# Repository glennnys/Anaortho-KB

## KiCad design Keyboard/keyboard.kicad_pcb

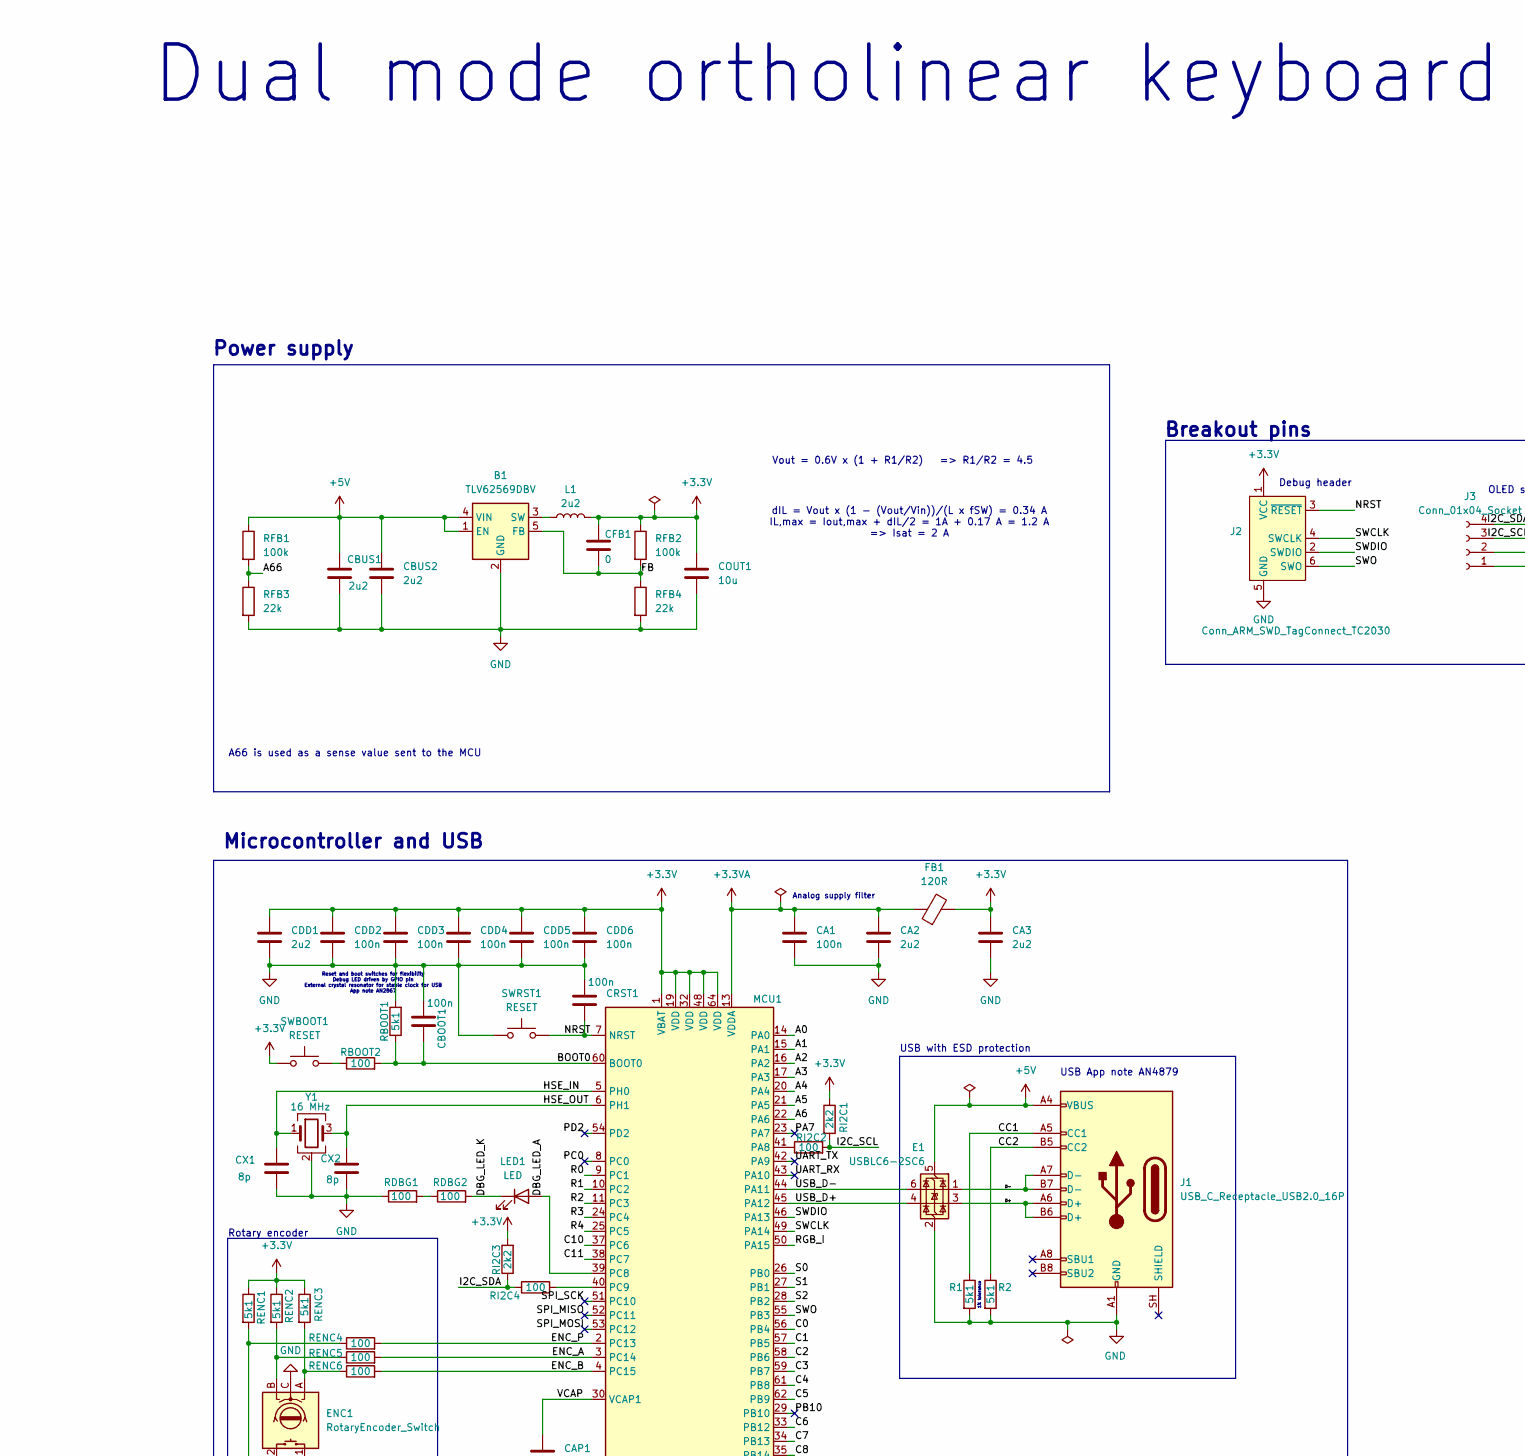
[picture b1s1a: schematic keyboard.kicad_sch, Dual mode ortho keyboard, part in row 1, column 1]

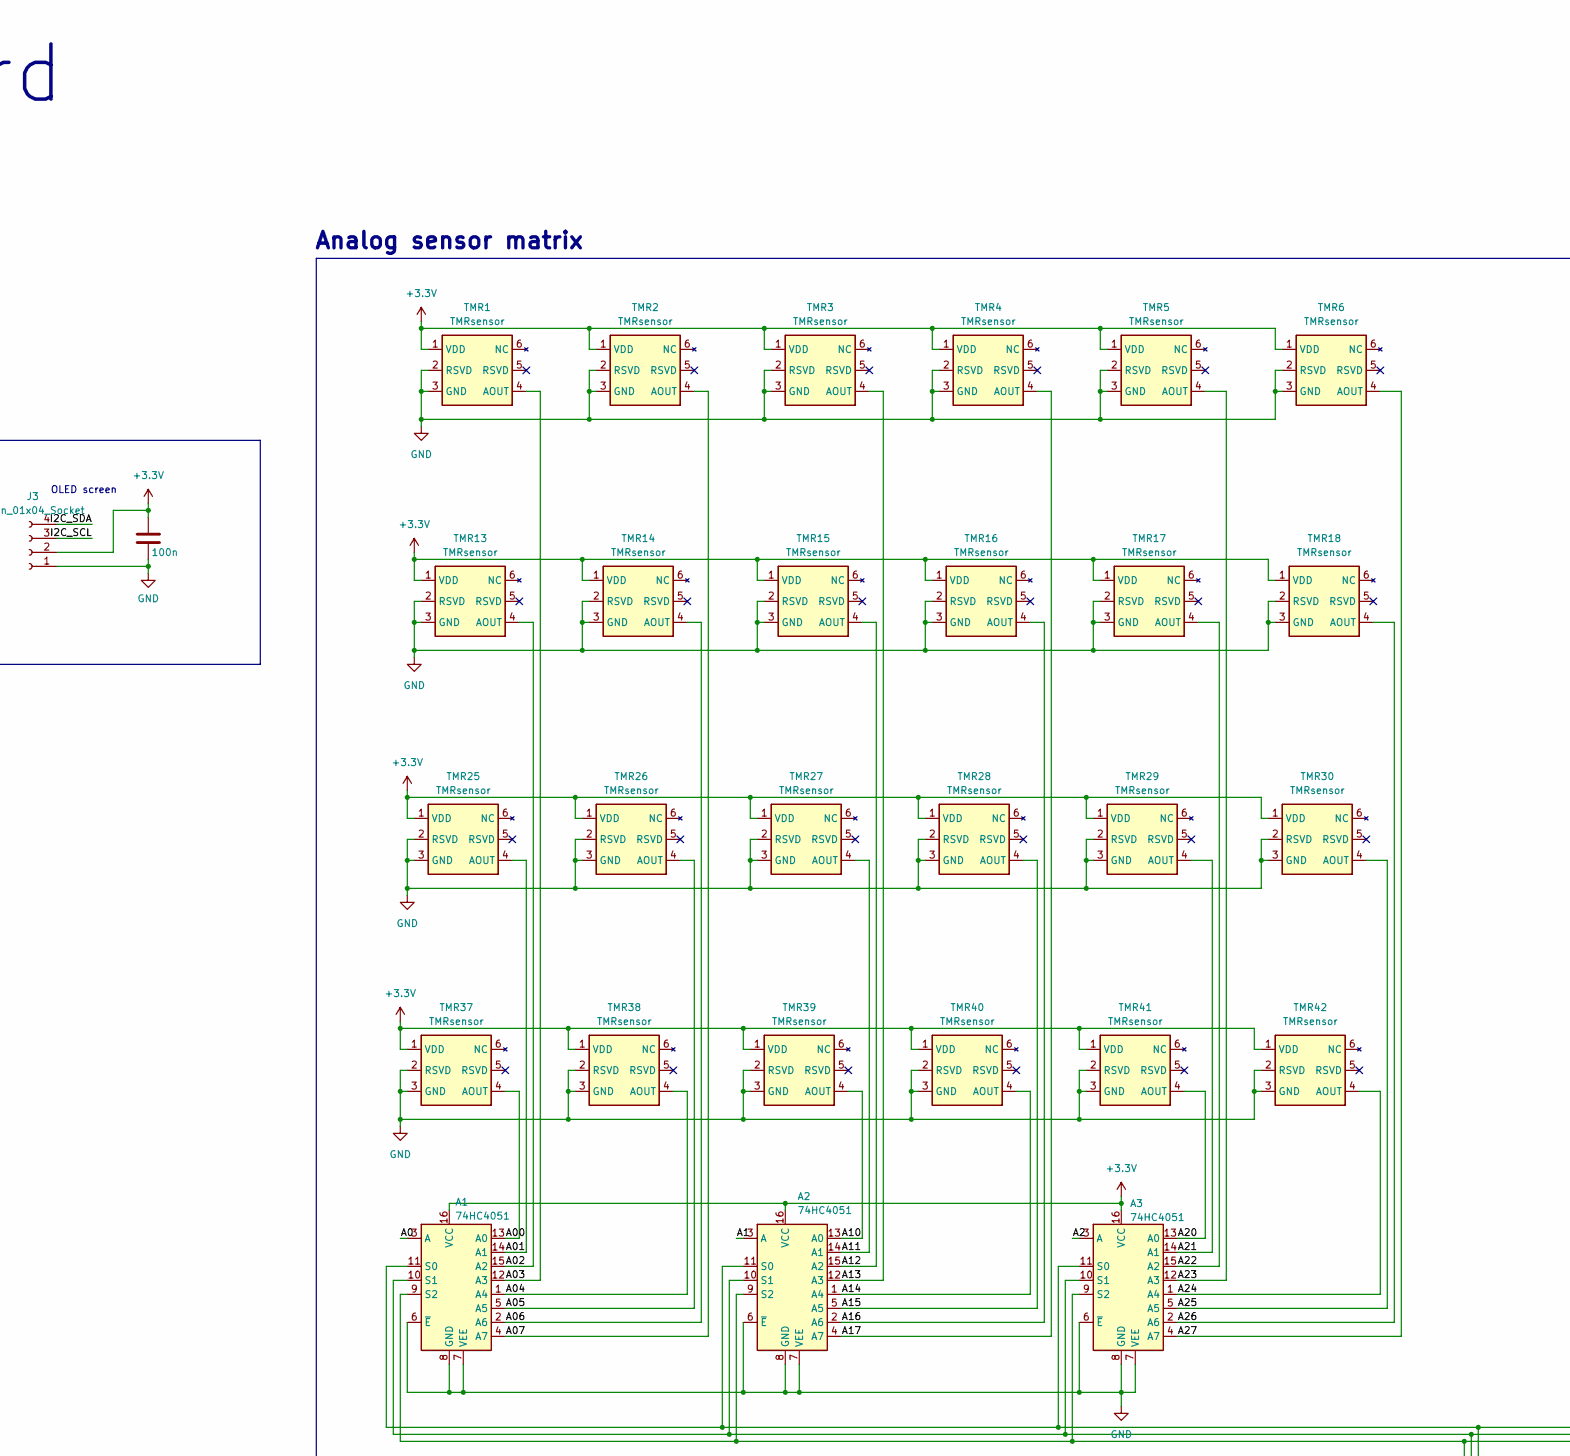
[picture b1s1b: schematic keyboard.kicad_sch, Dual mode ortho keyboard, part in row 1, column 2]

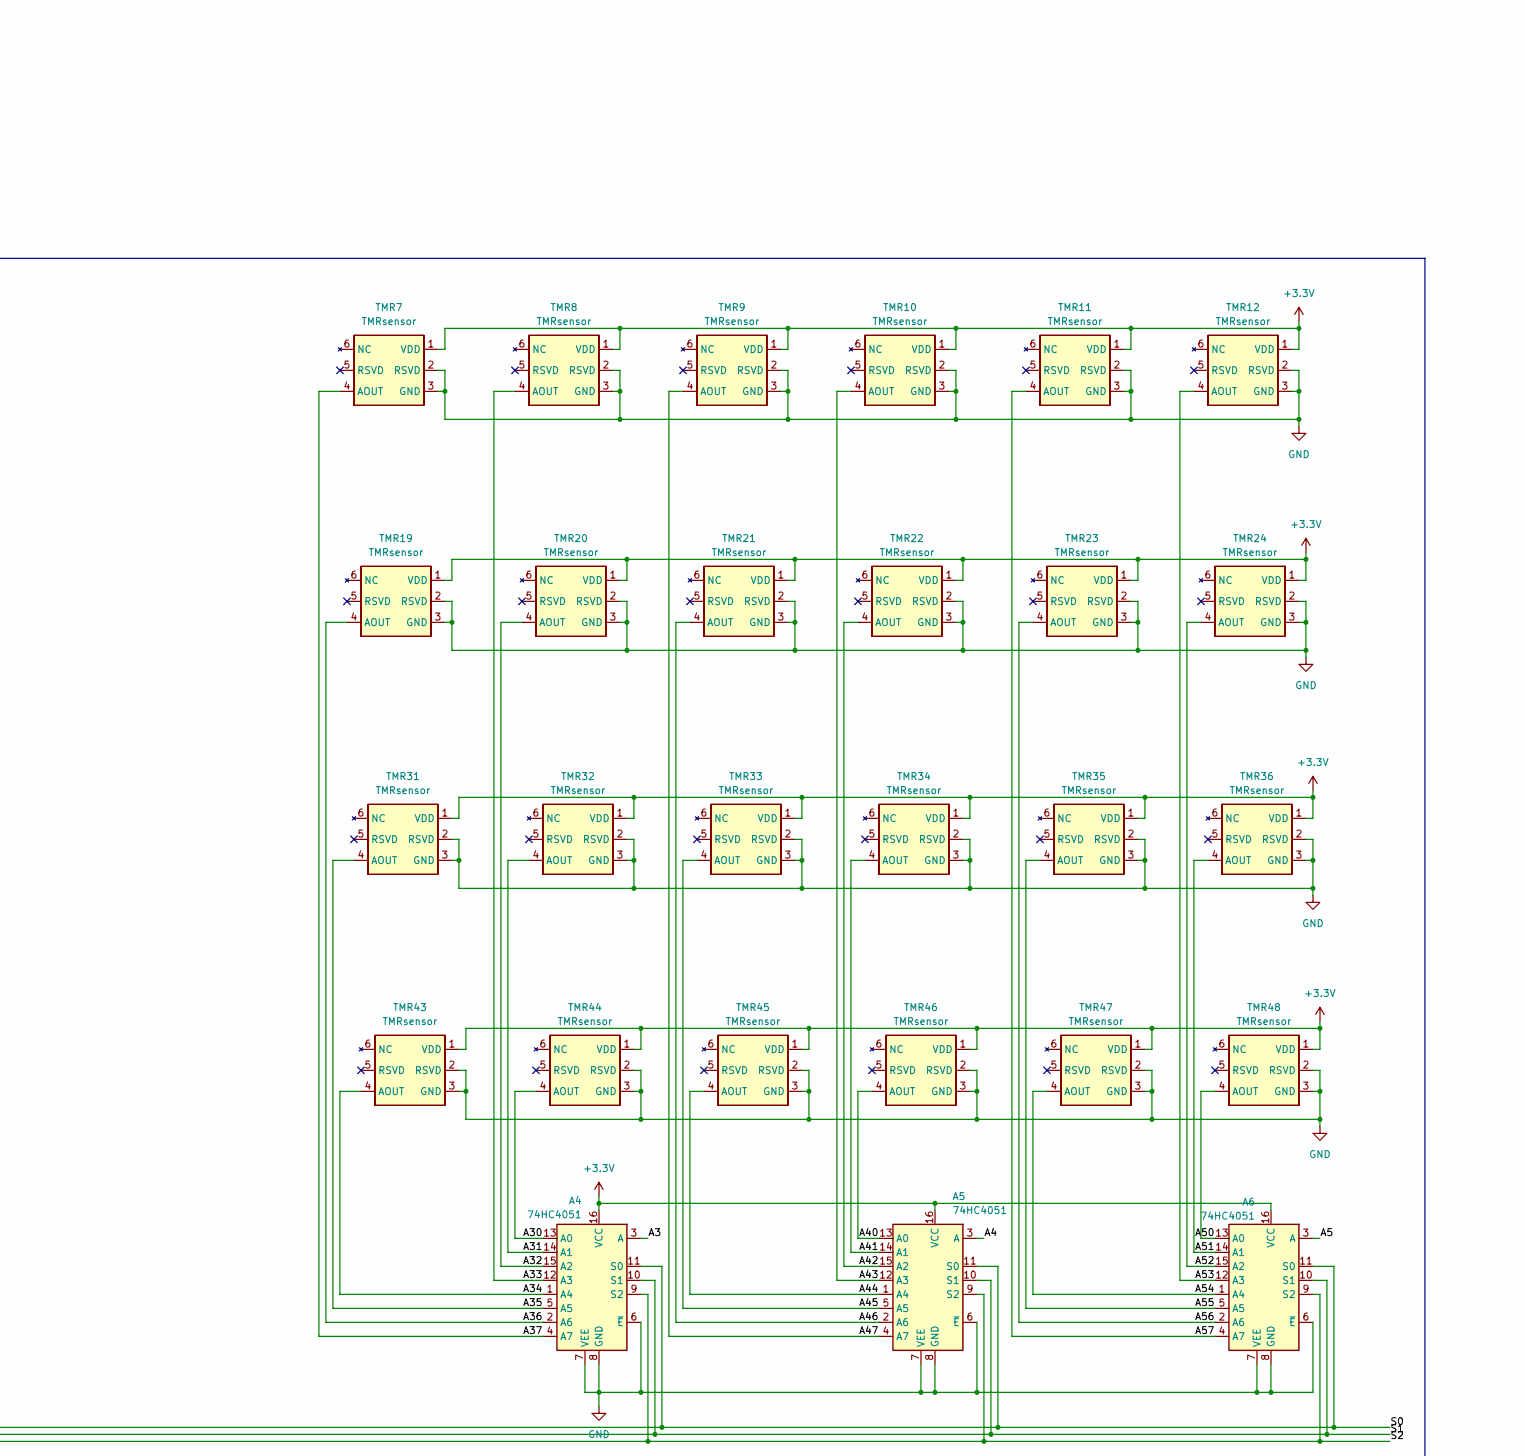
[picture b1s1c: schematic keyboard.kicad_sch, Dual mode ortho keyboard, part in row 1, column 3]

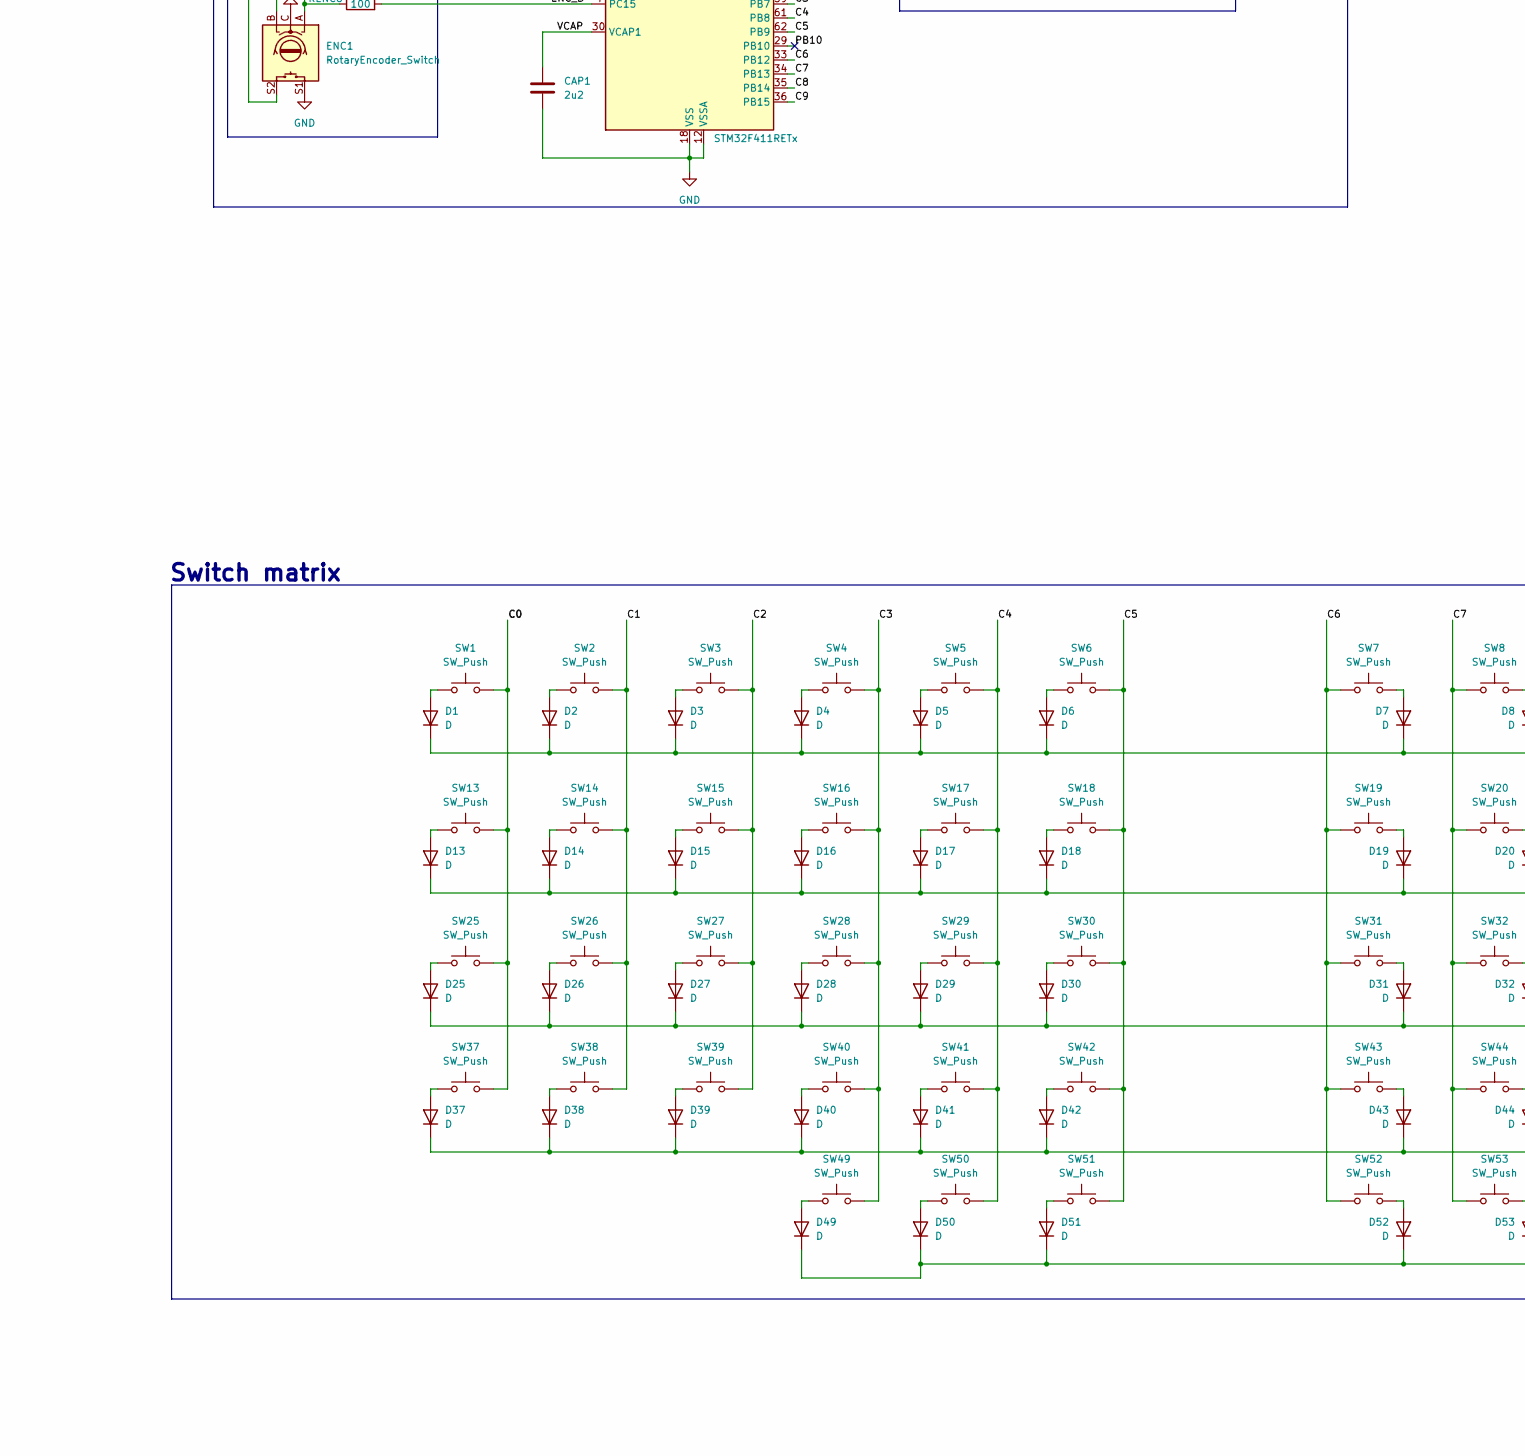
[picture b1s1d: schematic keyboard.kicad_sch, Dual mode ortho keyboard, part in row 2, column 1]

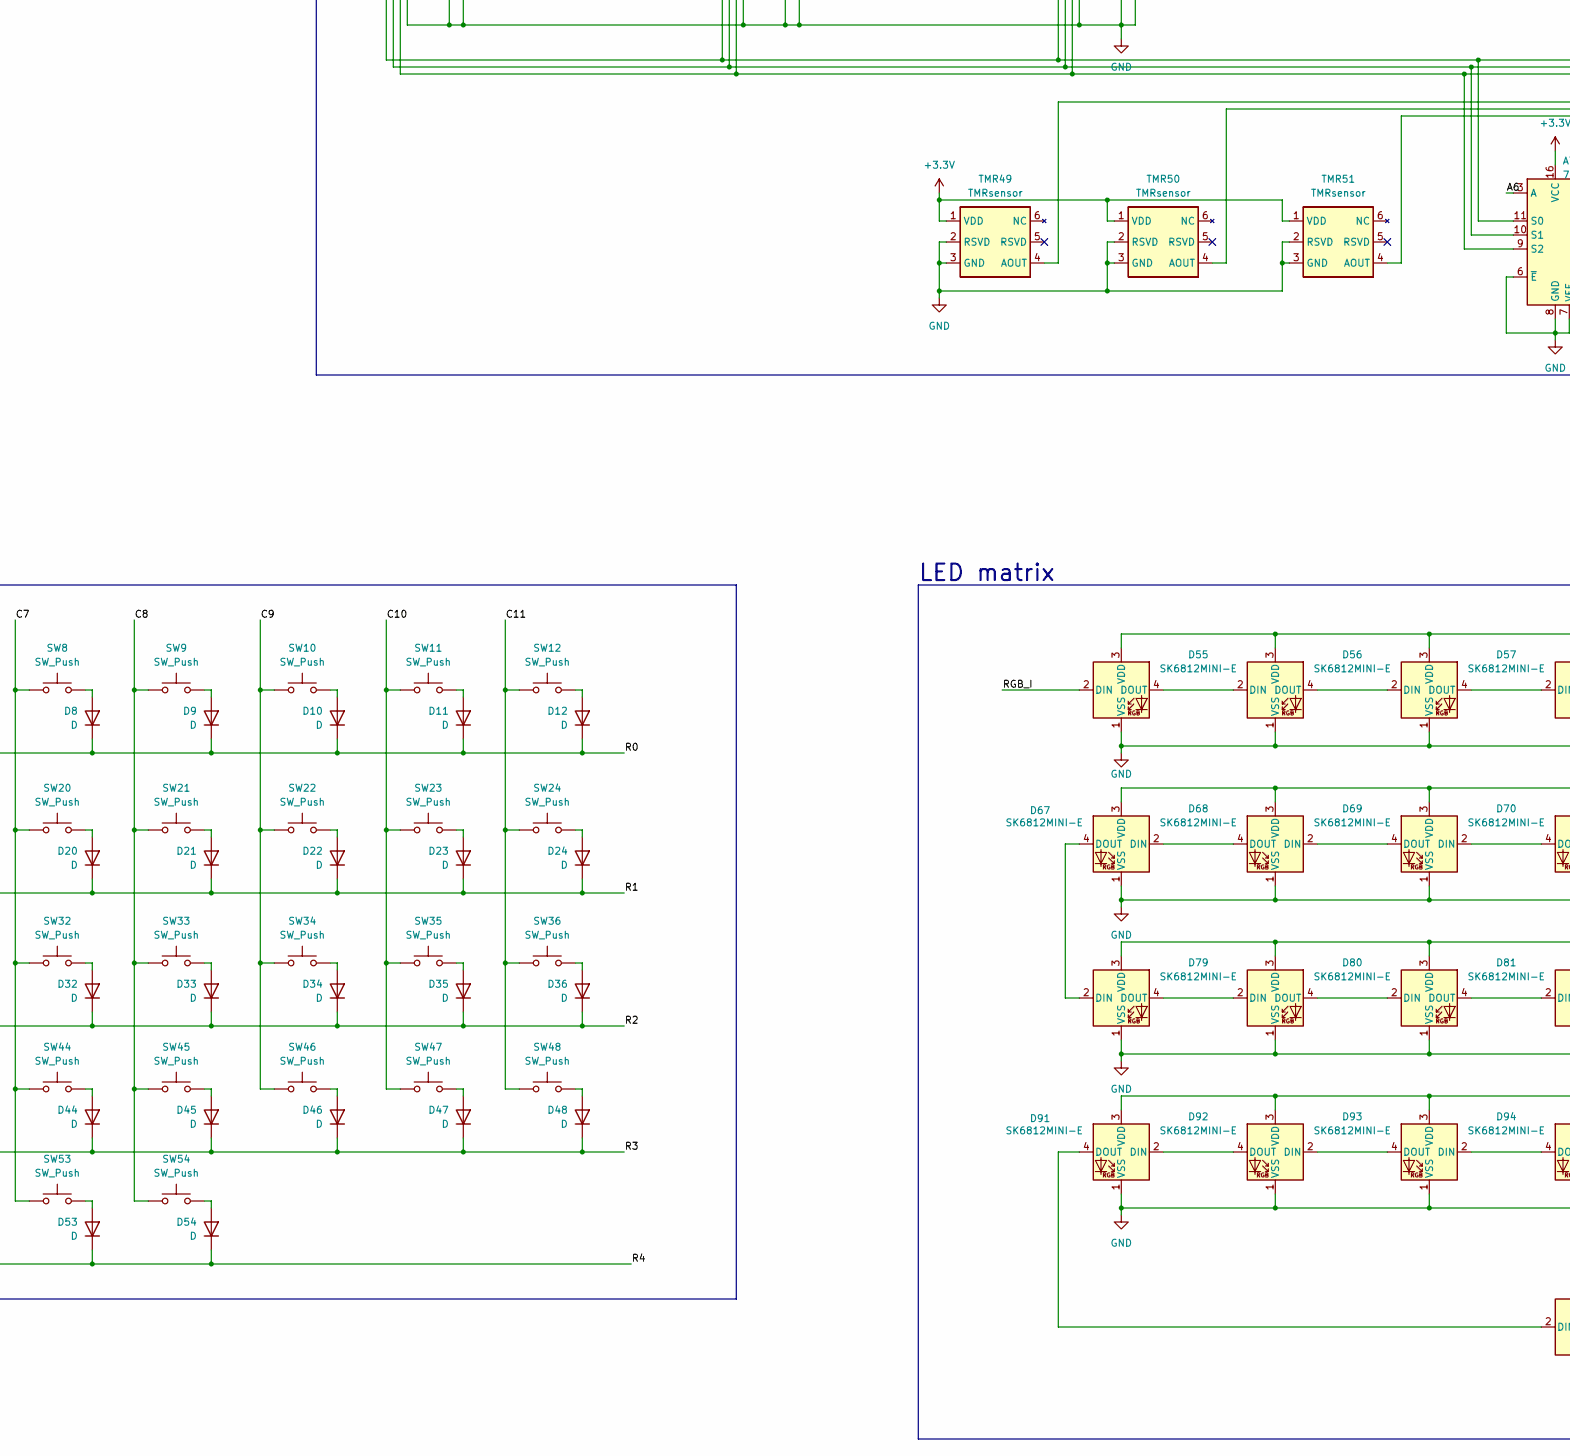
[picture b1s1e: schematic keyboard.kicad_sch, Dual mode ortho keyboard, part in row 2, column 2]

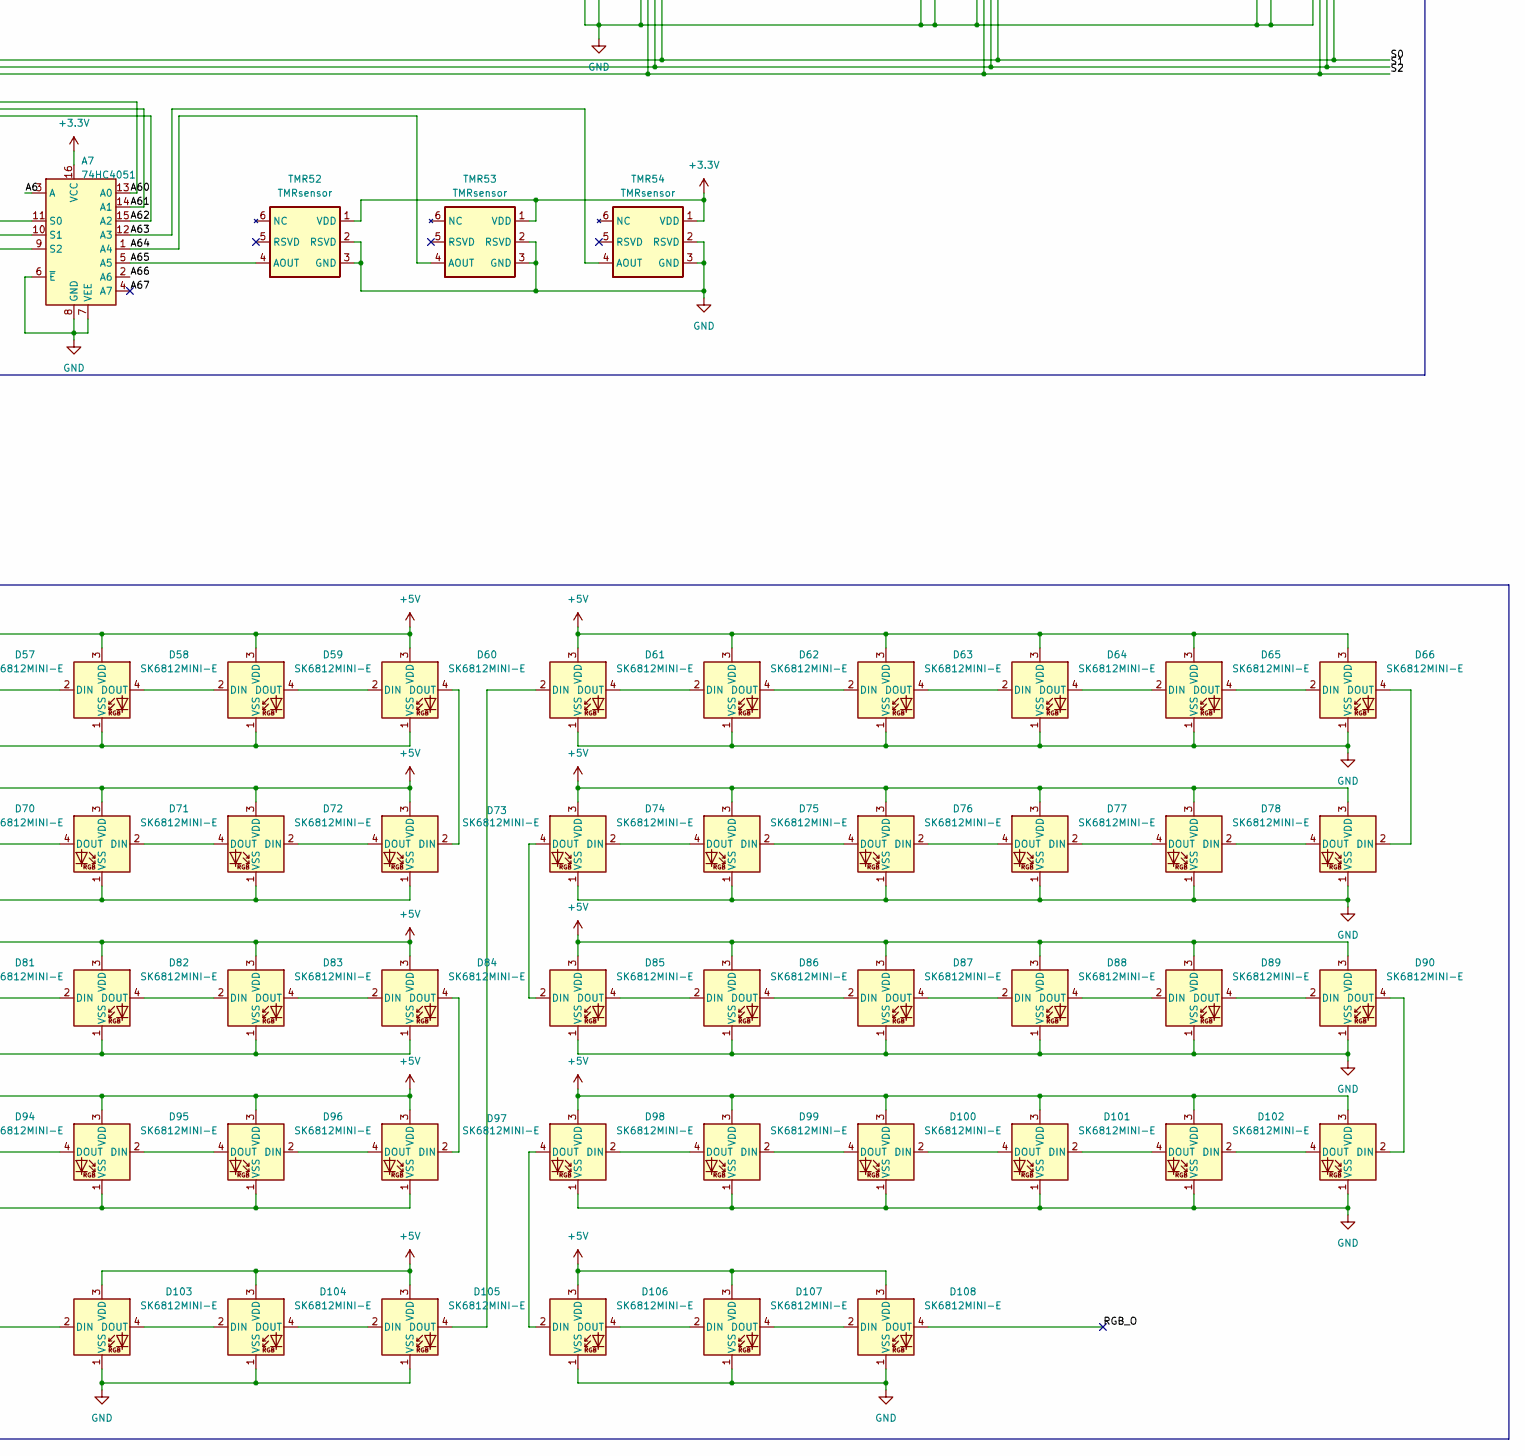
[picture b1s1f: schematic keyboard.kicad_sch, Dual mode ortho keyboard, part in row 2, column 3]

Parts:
A1, A2, A3, A4, A5, A6, A7: 74HC4051; SOIC-16W_5.3x10.2mm_P1.27mm
B1: TLV62569DBV; SOT-23-5
CA1: 100n; C_0402_1005Metric
CA2, CA3: 2u2; C_0603_1608Metric
CAP1: 2u2; C_0603_1608Metric
CBOOT1: 100n; C_0402_1005Metric
CBUS1, CBUS2: 2u2; C_0603_1608Metric
CDD1: 2u2; C_0603_1608Metric
CDD2, CDD3, CDD4, CDD5, CDD6: 100n; C_0402_1005Metric
CFB1: 0; C_0402_1005Metric
COLED1: 100n; C_0402_1005Metric
COUT1: 10u; C_0805_2012Metric
CRST1: 100n; C_0402_1005Metric
CX1, CX2: 8p; C_0402_1005Metric
D1, D2, D3, D4, D5, D6, D7, D8, D9, D10, D11, D12, D13, D14, D15, D16, D17, D18, D19, D20, D21, D22, D23, D24, D25, D26, D27, D28, D29, D30, D31, D32, D33, D34, D35, D36, D37, D38, D39, D40, D41, D42, D43, D44, D45, D46, D47, D48, D49, D50, D51, D52, D53, D54: D; D_SOD-123
D55, D56, D57, D58, D59, D60, D61, D62, D63, D64, D65, D66, D67, D68, D69, D70, D71, D72, D73, D74, D75, D76, D77, D78, D79, D80, D81, D82, D83, D84, D85, D86, D87, D88, D89, D90, D91, D92, D93, D94, D95, D96, D97, D98, D99, D100, D101, D102, D103, D104, D105, D106, D107, D108: SK6812MINI-E; LED_SK6812MINI-E_3.2x2.8mm_P1.5mm_ReverseMount
E1: USBLC6-2SC6; SOT-23-6
ENC1: RotaryEncoder_Switch; RotaryEncoder_Alps_EC11E-Switch_Vertical_H20mm
FB1: 120R; L_0603_1608Metric
J1: USB_C_Receptacle_USB2.0_16P; USB_C_Receptacle_GCT_USB4105-xx-A_16P_TopMnt_Horizontal
J2: Conn_ARM_SWD_TagConnect_TC2030; Tag-Connect_TC2030-IDC-FP_2x03_P1.27mm_Vertical
J3: Conn_01x04_Socket; PinSocket_1x04_P2.54mm_Vertical
L1: 2u2; L_0805_2012Metric
LED1: LED; LED_D4.0mm
MCU1: STM32F411RETx; LQFP-64_10x10mm_P0.5mm
R1, R2: 5k1; R_0402_1005Metric
RBOOT1: 5k1; R_0402_1005Metric
RBOOT2: 100; R_0402_1005Metric
RDBG1, RDBG2: 100; R_0402_1005Metric
RENC1, RENC2, RENC3: 5k1; R_0402_1005Metric
RENC4, RENC5, RENC6: 100; R_0402_1005Metric
RFB1, RFB2: 100k; R_0402_1005Metric
RFB3, RFB4: 22k; R_0402_1005Metric
RI2C1, RI2C3: 2k2; R_0402_1005Metric
RI2C2, RI2C4: 100; R_0402_1005Metric
SW1, SW2, SW3, SW4, SW5, SW6, SW7, SW8, SW9, SW10, SW11, SW12, SW13, SW14, SW15, SW16, SW17, SW18, SW19, SW20, SW21, SW22, SW23, SW24, SW25, SW26, SW27, SW28, SW29, SW30, SW31, SW32, SW33, SW34, SW35, SW36, SW37, SW38, SW39, SW40, SW41, SW42, SW43, SW44, SW45, SW46, SW47, SW48, SW49, SW50, SW51, SW52, SW53, SW54: SW_Push; SW_Cherry_MX_1.00u_PCB
SWBOOT1: RESET; SW_PUSH_6mm
SWRST1: RESET; SW_PUSH_6mm
TMR1, TMR2, TMR3, TMR4, TMR5, TMR6, TMR7, TMR8, TMR9, TMR10, TMR11, TMR12, TMR13, TMR14, TMR15, TMR16, TMR17, TMR18, TMR19, TMR20, TMR21, TMR22, TMR23, TMR24, TMR25, TMR26, TMR27, TMR28, TMR29, TMR30, TMR31, TMR32, TMR33, TMR34, TMR35, TMR36, TMR37, TMR38, TMR39, TMR40, TMR41, TMR42, TMR43, TMR44, TMR45, TMR46, TMR47, TMR48, TMR49, TMR50, TMR51, TMR52, TMR53, TMR54: TMRsensor; SOT-23-6
Y1: 16 MHz; Crystal_SMD_3225-4Pin_3.2x2.5mm

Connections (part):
+3.3V: A1.16 (VCC), A2.16 (VCC), A3.16 (VCC), A4.16 (VCC), A5.16 (VCC), A6.16 (VCC), A7.16 (VCC), CA3.1, CDD1.1, CDD2.1, CDD3.1, CDD4.1, CDD5.1, CDD6.1, CFB1.1, COLED1.1, COUT1.1, FB1.2, J2.1 (VCC), J3.2, L1.2, MCU1.1 (VBAT), MCU1.19 (VDD), MCU1.32 (VDD), MCU1.48 (VDD), MCU1.64 (VDD), RENC1.1, RENC2.1, RENC3.1, RFB2.1, RI2C1.1, RI2C3.2, SWBOOT1.1, TMR1.1 (VDD), TMR2.1 (VDD), TMR3.1 (VDD), TMR4.1 (VDD), TMR5.1 (VDD), TMR6.1 (VDD), TMR7.1 (VDD), TMR8.1 (VDD), TMR9.1 (VDD), TMR10.1 (VDD), TMR11.1 (VDD), TMR12.1 (VDD), TMR13.1 (VDD), TMR14.1 (VDD), TMR15.1 (VDD), TMR16.1 (VDD), TMR17.1 (VDD), TMR18.1 (VDD), TMR19.1 (VDD), TMR20.1 (VDD), TMR21.1 (VDD), TMR22.1 (VDD), TMR23.1 (VDD), TMR24.1 (VDD), TMR25.1 (VDD), TMR26.1 (VDD), TMR27.1 (VDD), TMR28.1 (VDD), TMR29.1 (VDD), TMR30.1 (VDD), TMR31.1 (VDD), TMR32.1 (VDD), TMR33.1 (VDD), TMR34.1 (VDD), TMR35.1 (VDD), TMR36.1 (VDD), TMR37.1 (VDD), TMR38.1 (VDD), TMR39.1 (VDD), TMR40.1 (VDD), TMR41.1 (VDD), TMR42.1 (VDD), TMR43.1 (VDD), TMR44.1 (VDD), TMR45.1 (VDD), TMR46.1 (VDD), TMR47.1 (VDD)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
+3.3VA: CA1.1, CA2.1, FB1.1, MCU1.13 (VDDA)
+5V: B1.1 (EN), B1.4 (VIN), CBUS1.1, CBUS2.1, D55.3 (VDD), D56.3 (VDD), D57.3 (VDD), D58.3 (VDD), D59.3 (VDD), D60.3 (VDD), D61.3 (VDD), D62.3 (VDD), D63.3 (VDD), D64.3 (VDD), D65.3 (VDD), D66.3 (VDD), D67.3 (VDD), D68.3 (VDD), D69.3 (VDD), D70.3 (VDD), D71.3 (VDD), D72.3 (VDD), D73.3 (VDD), D74.3 (VDD), D75.3 (VDD), D76.3 (VDD), D77.3 (VDD), D78.3 (VDD), D79.3 (VDD), D80.3 (VDD), D81.3 (VDD), D82.3 (VDD), D83.3 (VDD), D84.3 (VDD), D85.3 (VDD), D86.3 (VDD), D87.3 (VDD), D88.3 (VDD), D89.3 (VDD), D90.3 (VDD), D91.3 (VDD), D92.3 (VDD), D93.3 (VDD), D94.3 (VDD), D95.3 (VDD), D96.3 (VDD), D97.3 (VDD), D98.3 (VDD), D99.3 (VDD), D100.3 (VDD), D101.3 (VDD), D102.3 (VDD), D103.3 (VDD), D104.3 (VDD), D105.3 (VDD), D106.3 (VDD), D107.3 (VDD), D108.3 (VDD), E1.5 (VBUS), J1.A4 (VBUS), J1.A9 (VBUS), J1.B4 (VBUS), J1.B9 (VBUS), RFB1.1
/A0: A1.3 (A), MCU1.14 (PA0)
/A00: A1.13 (A0), TMR37.4 (AOUT)
/A1: A2.3 (A), MCU1.15 (PA1)
/A01: A1.14 (A1), TMR25.4 (AOUT)
/A2: A3.3 (A), MCU1.16 (PA2)
/A02: A1.15 (A2), TMR13.4 (AOUT)
/A3: A4.3 (A), MCU1.17 (PA3)
/A03: A1.12 (A3), TMR1.4 (AOUT)
/A4: A5.3 (A), MCU1.20 (PA4)
/A04: A1.1 (A4), TMR38.4 (AOUT)
/A5: A6.3 (A), MCU1.21 (PA5)
/A05: A1.5 (A5), TMR26.4 (AOUT)
/A6: A7.3 (A), MCU1.22 (PA6)
/A06: A1.2 (A6), TMR14.4 (AOUT)
/A07: A1.4 (A7), TMR2.4 (AOUT)
/A10: A2.13 (A0), TMR39.4 (AOUT)
/A11: A2.14 (A1), TMR27.4 (AOUT)
/A12: A2.15 (A2), TMR15.4 (AOUT)
/A13: A2.12 (A3), TMR3.4 (AOUT)
/A14: A2.1 (A4), TMR40.4 (AOUT)
/A15: A2.5 (A5), TMR28.4 (AOUT)
/A16: A2.2 (A6), TMR16.4 (AOUT)
/A17: A2.4 (A7), TMR4.4 (AOUT)
/A20: A3.13 (A0), TMR41.4 (AOUT)
/A21: A3.14 (A1), TMR29.4 (AOUT)
/A22: A3.15 (A2), TMR17.4 (AOUT)
/A23: A3.12 (A3), TMR5.4 (AOUT)
/A24: A3.1 (A4), TMR42.4 (AOUT)
/A25: A3.5 (A5), TMR30.4 (AOUT)
/A26: A3.2 (A6), TMR18.4 (AOUT)
/A27: A3.4 (A7), TMR6.4 (AOUT)
/A30: A4.13 (A0), TMR44.4 (AOUT)
/A31: A4.14 (A1), TMR32.4 (AOUT)
/A32: A4.15 (A2), TMR20.4 (AOUT)
/A33: A4.12 (A3), TMR8.4 (AOUT)
/A34: A4.1 (A4), TMR43.4 (AOUT)
/A35: A4.5 (A5), TMR31.4 (AOUT)
/A36: A4.2 (A6), TMR19.4 (AOUT)
/A37: A4.4 (A7), TMR7.4 (AOUT)
/A40: A5.13 (A0), TMR46.4 (AOUT)
/A41: A5.14 (A1), TMR34.4 (AOUT)
/A42: A5.15 (A2), TMR22.4 (AOUT)
/A43: A5.12 (A3), TMR10.4 (AOUT)
/A44: A5.1 (A4), TMR45.4 (AOUT)
/A45: A5.5 (A5), TMR33.4 (AOUT)
/A46: A5.2 (A6), TMR21.4 (AOUT)
/A47: A5.4 (A7), TMR9.4 (AOUT)
/A50: A6.13 (A0), TMR48.4 (AOUT)
/A51: A6.14 (A1), TMR36.4 (AOUT)
/A52: A6.15 (A2), TMR24.4 (AOUT)
/A53: A6.12 (A3), TMR12.4 (AOUT)
/A54: A6.1 (A4), TMR47.4 (AOUT)
/A55: A6.5 (A5), TMR35.4 (AOUT)
/A56: A6.2 (A6), TMR23.4 (AOUT)
/A57: A6.4 (A7), TMR11.4 (AOUT)
/A60: A7.13 (A0), TMR49.4 (AOUT)
/A61: A7.14 (A1), TMR50.4 (AOUT)
/A62: A7.15 (A2), TMR51.4 (AOUT)
/A63: A7.12 (A3), TMR54.4 (AOUT)
/A64: A7.1 (A4), TMR53.4 (AOUT)
/A65: A7.5 (A5), TMR52.4 (AOUT)
/A66: A7.2 (A6), RFB1.2, RFB3.1
/A67: A7.4 (A7)
/BOOT0: CBOOT1.2, MCU1.60 (BOOT0), RBOOT1.1, RBOOT2.2
/C0: MCU1.56 (PB4), SW1.2, SW13.2, SW25.2, SW37.2
/C1: MCU1.57 (PB5), SW2.2, SW14.2, SW26.2, SW38.2
/C2: MCU1.58 (PB6), SW3.2, SW15.2, SW27.2, SW39.2
/C3: MCU1.59 (PB7), SW4.2, SW16.2, SW28.2, SW40.2, SW49.2
/C4: MCU1.61 (PB8), SW5.2, SW17.2, SW29.2, SW41.2, SW50.2
/C5: MCU1.62 (PB9), SW6.2, SW18.2, SW30.2, SW42.2, SW51.2
/C6: MCU1.33 (PB12), SW7.2, SW19.2, SW31.2, SW43.2, SW52.2
/C7: MCU1.34 (PB13), SW8.2, SW20.2, SW32.2, SW44.2, SW53.2
/C8: MCU1.35 (PB14), SW9.2, SW21.2, SW33.2, SW45.2, SW54.2
/C9: MCU1.36 (PB15), SW10.2, SW22.2, SW34.2, SW46.2
/C10: MCU1.37 (PC6), SW11.2, SW23.2, SW35.2, SW47.2
/C11: MCU1.38 (PC7), SW12.2, SW24.2, SW36.2, SW48.2
/CC1: J1.A5 (CC1), R1.1
/CC2: J1.B5 (CC2), R2.1
/D+: E1.3 (I/O2), J1.A6 (D+), J1.B6 (D+)
/D-: E1.1 (I/O1), J1.A7 (D-), J1.B7 (D-)
/DBG_LED_A: LED1.2 (A), MCU1.39 (PC8)
/DBG_LED_K: LED1.1 (K), RDBG2.2
/ENC_A: MCU1.3 (PC14), RENC5.2
/ENC_B: MCU1.4 (PC15), RENC6.2
/ENC_P: MCU1.2 (PC13), RENC4.2
/FB: B1.5 (FB), CFB1.2, RFB2.2, RFB4.1
/HSE_IN: CX1.1, MCU1.5 (PH0), Y1.1
/HSE_OUT: CX2.1, MCU1.6 (PH1), Y1.3
/I2C_SCL: J3.3, RI2C1.2, RI2C2.2
/I2C_SDA: J3.4, RI2C3.1, RI2C4.1
/NRST: CRST1.2, J2.3 (~RESET), MCU1.7 (NRST), SWRST1.2
/PA7: MCU1.23 (PA7)
/PB10: MCU1.29 (PB10)
/PC0: MCU1.8 (PC0)
/PD2: MCU1.54 (PD2)
/R0: D1.1 (K), D2.1 (K), D3.1 (K), D4.1 (K), D5.1 (K), D6.1 (K), D7.1 (K), D8.1 (K), D9.1 (K), D10.1 (K), D11.1 (K), D12.1 (K), MCU1.9 (PC1)
/R1: D13.1 (K), D14.1 (K), D15.1 (K), D16.1 (K), D17.1 (K), D18.1 (K), D19.1 (K), D20.1 (K), D21.1 (K), D22.1 (K), D23.1 (K), D24.1 (K), MCU1.10 (PC2)
/R2: D25.1 (K), D26.1 (K), D27.1 (K), D28.1 (K), D29.1 (K), D30.1 (K), D31.1 (K), D32.1 (K), D33.1 (K), D34.1 (K), D35.1 (K), D36.1 (K), MCU1.11 (PC3)
/R3: D37.1 (K), D38.1 (K), D39.1 (K), D40.1 (K), D41.1 (K), D42.1 (K), D43.1 (K), D44.1 (K), D45.1 (K), D46.1 (K), D47.1 (K), D48.1 (K), MCU1.24 (PC4)
/R4: D49.1 (K), D50.1 (K), D51.1 (K), D52.1 (K), D53.1 (K), D54.1 (K), MCU1.25 (PC5)
/RGB_I: D55.2 (DIN), MCU1.50 (PA15)
/RGB_O: D108.4 (DOUT)
/S0: A1.11 (S0), A2.11 (S0), A3.11 (S0), A4.11 (S0), A5.11 (S0), A6.11 (S0), A7.11 (S0), MCU1.26 (PB0)
/S1: A1.10 (S1), A2.10 (S1), A3.10 (S1), A4.10 (S1), A5.10 (S1), A6.10 (S1), A7.10 (S1), MCU1.27 (PB1)
/S2: A1.9 (S2), A2.9 (S2), A3.9 (S2), A4.9 (S2), A5.9 (S2), A6.9 (S2), A7.9 (S2), MCU1.28 (PB2)
/SPI_MISO: MCU1.52 (PC11)
/SPI_MOSI: MCU1.53 (PC12)
/SPI_SCK: MCU1.51 (PC10)
/SWCLK: J2.4 (SWCLK), MCU1.49 (PA14)
/SWDIO: J2.2 (SWDIO), MCU1.46 (PA13)
/SWO: J2.6 (SWO), MCU1.55 (PB3)
/UART_RX: MCU1.43 (PA10)
/UART_TX: MCU1.42 (PA9)
/USB_D+: E1.4 (I/O2), MCU1.45 (PA12)
/USB_D-: E1.6 (I/O1), MCU1.44 (PA11)
/VCAP: CAP1.1, MCU1.30 (VCAP1)
GND: A1.6 (~E), A1.7 (VEE), A1.8 (GND), A2.6 (~E), A2.7 (VEE), A2.8 (GND), A3.6 (~E), A3.7 (VEE), A3.8 (GND), A4.6 (~E), A4.7 (VEE), A4.8 (GND), A5.6 (~E), A5.7 (VEE), A5.8 (GND), A6.6 (~E), A6.7 (VEE), A6.8 (GND), A7.6 (~E), A7.7 (VEE), A7.8 (GND), B1.2 (GND), CA1.2, CA2.2, CA3.2, CAP1.2, CBOOT1.1, CBUS1.2, CBUS2.2, CDD1.2, CDD2.2, CDD3.2, CDD4.2, CDD5.2, CDD6.2, COLED1.2, COUT1.2, CRST1.1, CX1.2, CX2.2, D55.1 (VSS), D56.1 (VSS), D57.1 (VSS), D58.1 (VSS), D59.1 (VSS), D60.1 (VSS), D61.1 (VSS), D62.1 (VSS), D63.1 (VSS), D64.1 (VSS), D65.1 (VSS), D66.1 (VSS), D67.1 (VSS), D68.1 (VSS), D69.1 (VSS), D70.1 (VSS), D71.1 (VSS), D72.1 (VSS), D73.1 (VSS), D74.1 (VSS), D75.1 (VSS), D76.1 (VSS), D77.1 (VSS), D78.1 (VSS), D79.1 (VSS), D80.1 (VSS), D81.1 (VSS), D82.1 (VSS), D83.1 (VSS), D84.1 (VSS), D85.1 (VSS), D86.1 (VSS), D87.1 (VSS), D88.1 (VSS), D89.1 (VSS), D90.1 (VSS), D91.1 (VSS), D92.1 (VSS), D93.1 (VSS), D94.1 (VSS)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
unnamed: B1.3 (SW), L1.1
unnamed: D1.2 (A), SW1.1
unnamed: D2.2 (A), SW2.1
unnamed: D3.2 (A), SW3.1
unnamed: D4.2 (A), SW4.1
unnamed: D5.2 (A), SW5.1
unnamed: D6.2 (A), SW6.1
unnamed: D7.2 (A), SW7.1
unnamed: D8.2 (A), SW8.1
unnamed: D9.2 (A), SW9.1
unnamed: D10.2 (A), SW10.1
unnamed: D11.2 (A), SW11.1
unnamed: D12.2 (A), SW12.1
unnamed: D13.2 (A), SW13.1
unnamed: D14.2 (A), SW14.1
unnamed: D15.2 (A), SW15.1
unnamed: D16.2 (A), SW16.1
unnamed: D17.2 (A), SW17.1
unnamed: D18.2 (A), SW18.1
unnamed: D19.2 (A), SW19.1
unnamed: D20.2 (A), SW20.1
unnamed: D21.2 (A), SW21.1
unnamed: D22.2 (A), SW22.1
unnamed: D23.2 (A), SW23.1
unnamed: D24.2 (A), SW24.1
unnamed: D25.2 (A), SW25.1
unnamed: D26.2 (A), SW26.1
unnamed: D27.2 (A), SW27.1
unnamed: D28.2 (A), SW28.1
unnamed: D29.2 (A), SW29.1
unnamed: D30.2 (A), SW30.1
unnamed: D31.2 (A), SW31.1
unnamed: D32.2 (A), SW32.1
unnamed: D33.2 (A), SW33.1
unnamed: D34.2 (A), SW34.1
unnamed: D35.2 (A), SW35.1
unnamed: D36.2 (A), SW36.1
unnamed: D37.2 (A), SW37.1
unnamed: D38.2 (A), SW38.1
unnamed: D39.2 (A), SW39.1
unnamed: D40.2 (A), SW40.1
unnamed: D41.2 (A), SW41.1
unnamed: D42.2 (A), SW42.1
unnamed: D43.2 (A), SW43.1
unnamed: D44.2 (A), SW44.1
unnamed: D45.2 (A), SW45.1
unnamed: D46.2 (A), SW46.1
unnamed: D47.2 (A), SW47.1
unnamed: D48.2 (A), SW48.1
unnamed: D49.2 (A), SW49.1
unnamed: D50.2 (A), SW50.1
unnamed: D51.2 (A), SW51.1
unnamed: D52.2 (A), SW52.1
unnamed: D53.2 (A), SW53.1
unnamed: D54.2 (A), SW54.1
unnamed: D55.4 (DOUT), D56.2 (DIN)
unnamed: D56.4 (DOUT), D57.2 (DIN)
unnamed: D57.4 (DOUT), D58.2 (DIN)
unnamed: D58.4 (DOUT), D59.2 (DIN)
unnamed: D59.4 (DOUT), D60.2 (DIN)
unnamed: D60.4 (DOUT), D72.2 (DIN)
unnamed: D61.4 (DOUT), D62.2 (DIN)
unnamed: D62.4 (DOUT), D63.2 (DIN)
unnamed: D63.4 (DOUT), D64.2 (DIN)
unnamed: D64.4 (DOUT), D65.2 (DIN)
unnamed: D65.4 (DOUT), D66.2 (DIN)
unnamed: D66.4 (DOUT), D78.2 (DIN)
unnamed: D67.2 (DIN), D68.4 (DOUT)
unnamed: D67.4 (DOUT), D79.2 (DIN)
unnamed: D68.2 (DIN), D69.4 (DOUT)
unnamed: D69.2 (DIN), D70.4 (DOUT)
unnamed: D70.2 (DIN), D71.4 (DOUT)
unnamed: D71.2 (DIN), D72.4 (DOUT)
unnamed: D73.2 (DIN), D74.4 (DOUT)
unnamed: D73.4 (DOUT), D85.2 (DIN)
unnamed: D74.2 (DIN), D75.4 (DOUT)
unnamed: D75.2 (DIN), D76.4 (DOUT)
unnamed: D76.2 (DIN), D77.4 (DOUT)
unnamed: D77.2 (DIN), D78.4 (DOUT)
unnamed: D79.4 (DOUT), D80.2 (DIN)
unnamed: D80.4 (DOUT), D81.2 (DIN)
unnamed: D81.4 (DOUT), D82.2 (DIN)
unnamed: D82.4 (DOUT), D83.2 (DIN)
unnamed: D83.4 (DOUT), D84.2 (DIN)
unnamed: D84.4 (DOUT), D96.2 (DIN)
unnamed: D85.4 (DOUT), D86.2 (DIN)
unnamed: D86.4 (DOUT), D87.2 (DIN)
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
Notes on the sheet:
Breakout pins
Power supply
Rotary encoder
LED matrix
Reset and boot switches for flexibility Debug LED driven by GPIO pin External crystal resonator for stable clock for USB App note AN2867
Vout = 0.6V x (1 + R1/R2)
1% tolerance
Dual mode ortholinear keyboard
Debug header
Switch matrix
dIL = Vout x (1 - (Vout/Vin))/(L x fSW) = 0.34 A IL,max = Iout,max + dIL/2 = 1A + 0.17 A = 1.2 A => Isat = 2 A
Microcontroller and USB
USB with ESD protection
Analog supply filter
Analog sensor matrix
OLED screen
=> R1/R2 = 4.5
USB App note AN4879
A66 is used as a sense value sent to the MCU

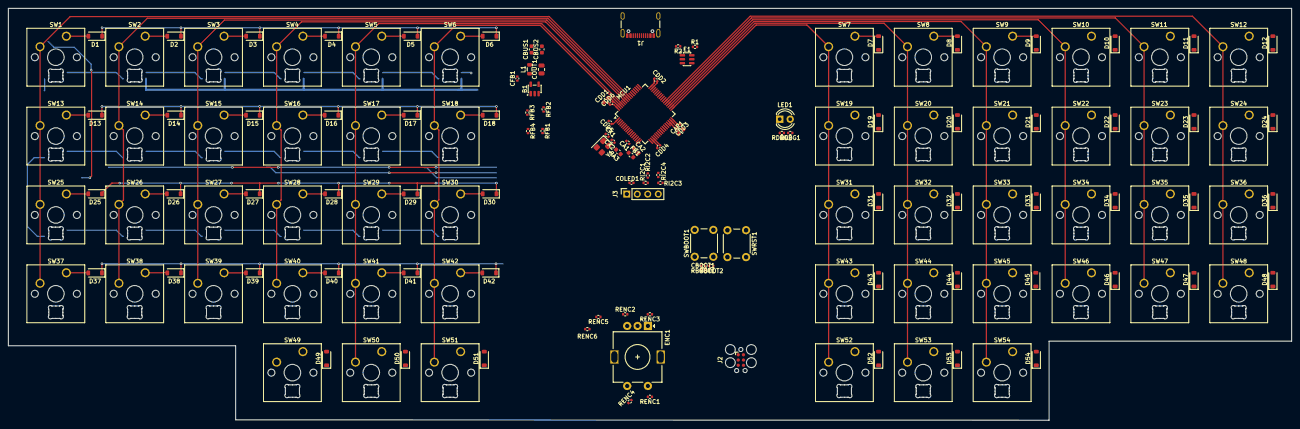
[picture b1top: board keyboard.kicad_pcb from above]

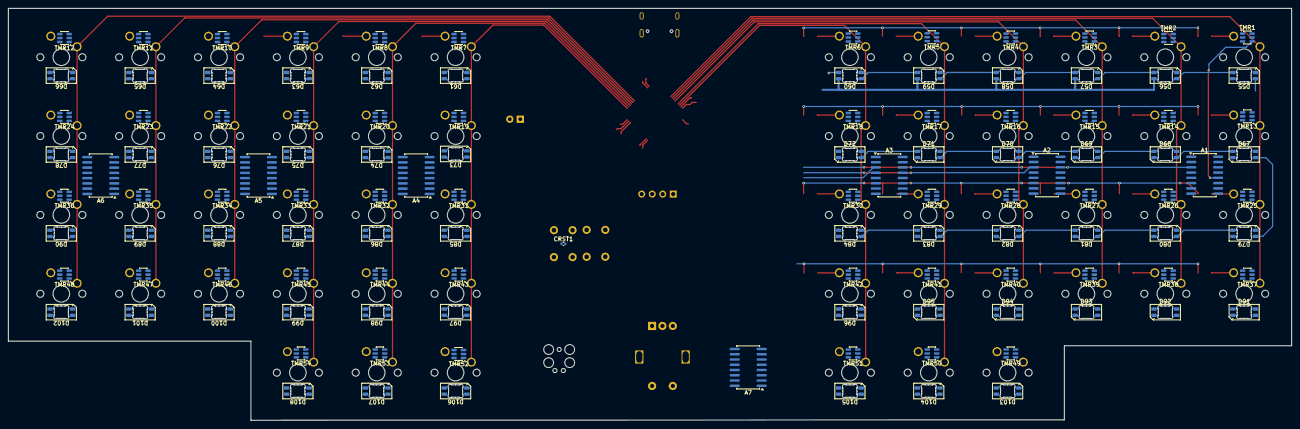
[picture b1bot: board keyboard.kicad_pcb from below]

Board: 4 copper layers, 310.0 x 99.5 mm, 275 parts (116 on the bottom side), 224 nets.

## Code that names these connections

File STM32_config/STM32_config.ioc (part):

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Mcu.Name=STM32F411R(C-E)Tx
Mcu.Package=LQFP64
Mcu.UserName=STM32F411RETx
PA0-WKUP.Signal=ADCx_IN0
PA1.Signal=ADCx_IN1
PA10.Mode=Asynchronous
PA10.Signal=USART1_RX
PA11.Mode=Device_Only
PA11.Signal=USB_OTG_FS_DM
PA12.Mode=Device_Only
PA12.Signal=USB_OTG_FS_DP
PA13.Mode=Trace_Asynchronous_SW
PA13.Signal=SYS_JTMS-SWDIO
PA14.Mode=Trace_Asynchronous_SW
PA14.Signal=SYS_JTCK-SWCLK
PA15.Signal=S_TIM2_CH1_ETR
PA2.Signal=ADCx_IN2
PA3.Signal=ADCx_IN3
PA4.Signal=ADCx_IN4
PA5.Signal=ADCx_IN5
PA6.Signal=ADCx_IN6
PA8.Mode=I2C
PA8.Signal=I2C3_SCL
PA9.Mode=Asynchronous
PA9.Signal=USART1_TX
PB0.Signal=GPIO_Output
PB1.Signal=GPIO_Output
PB12.Signal=GPIO_Output
PB13.Signal=GPIO_Output
PB14.Signal=GPIO_Output
PB15.Signal=GPIO_Output
PB2.Signal=GPIO_Output
PB3.Mode=Trace_Asynchronous_SW
PB3.Signal=SYS_JTDO-SWO
PB4.Signal=GPIO_Output
PB5.Signal=GPIO_Output
PB6.Signal=GPIO_Output
PB7.Signal=GPIO_Output
PB8.Signal=GPIO_Output
PB9.Signal=GPIO_Output
PC1.Signal=GPIO_Input
PC10.Mode=Full_Duplex_Master
PC10.Signal=SPI3_SCK
PC11.Mode=Full_Duplex_Master
PC11.Signal=SPI3_MISO
PC12.Mode=Full_Duplex_Master
PC12.Signal=SPI3_MOSI
PC13-ANTI_TAMP.Signal=GPIO_Input
PC14-OSC32_IN.Signal=GPIO_Input
PC15-OSC32_OUT.Signal=GPIO_Input
PC2.Signal=GPIO_Input
PC3.Signal=GPIO_Input
PC4.Signal=GPIO_Input
PC5.Signal=GPIO_Input
PC6.Signal=GPIO_Output
PC7.Signal=GPIO_Output
PC8.Signal=S_TIM3_CH3
PC9.Mode=I2C
PC9.Signal=I2C3_SDA
PH0\ -\ OSC_IN.Mode=HSE-External-Oscillator
PH0\ -\ OSC_IN.Signal=RCC_OSC_IN
PH1\ -\ OSC_OUT.Mode=HSE-External-Oscillator
PH1\ -\ OSC_OUT.Signal=RCC_OSC_OUT
RCC.HSE_VALUE=16000000
RCC.SYSCLKFreq_VALUE=96000000.00000001
RCC.SYSCLKSource=RCC_SYSCLKSOURCE_PLLCLK
board=custom
